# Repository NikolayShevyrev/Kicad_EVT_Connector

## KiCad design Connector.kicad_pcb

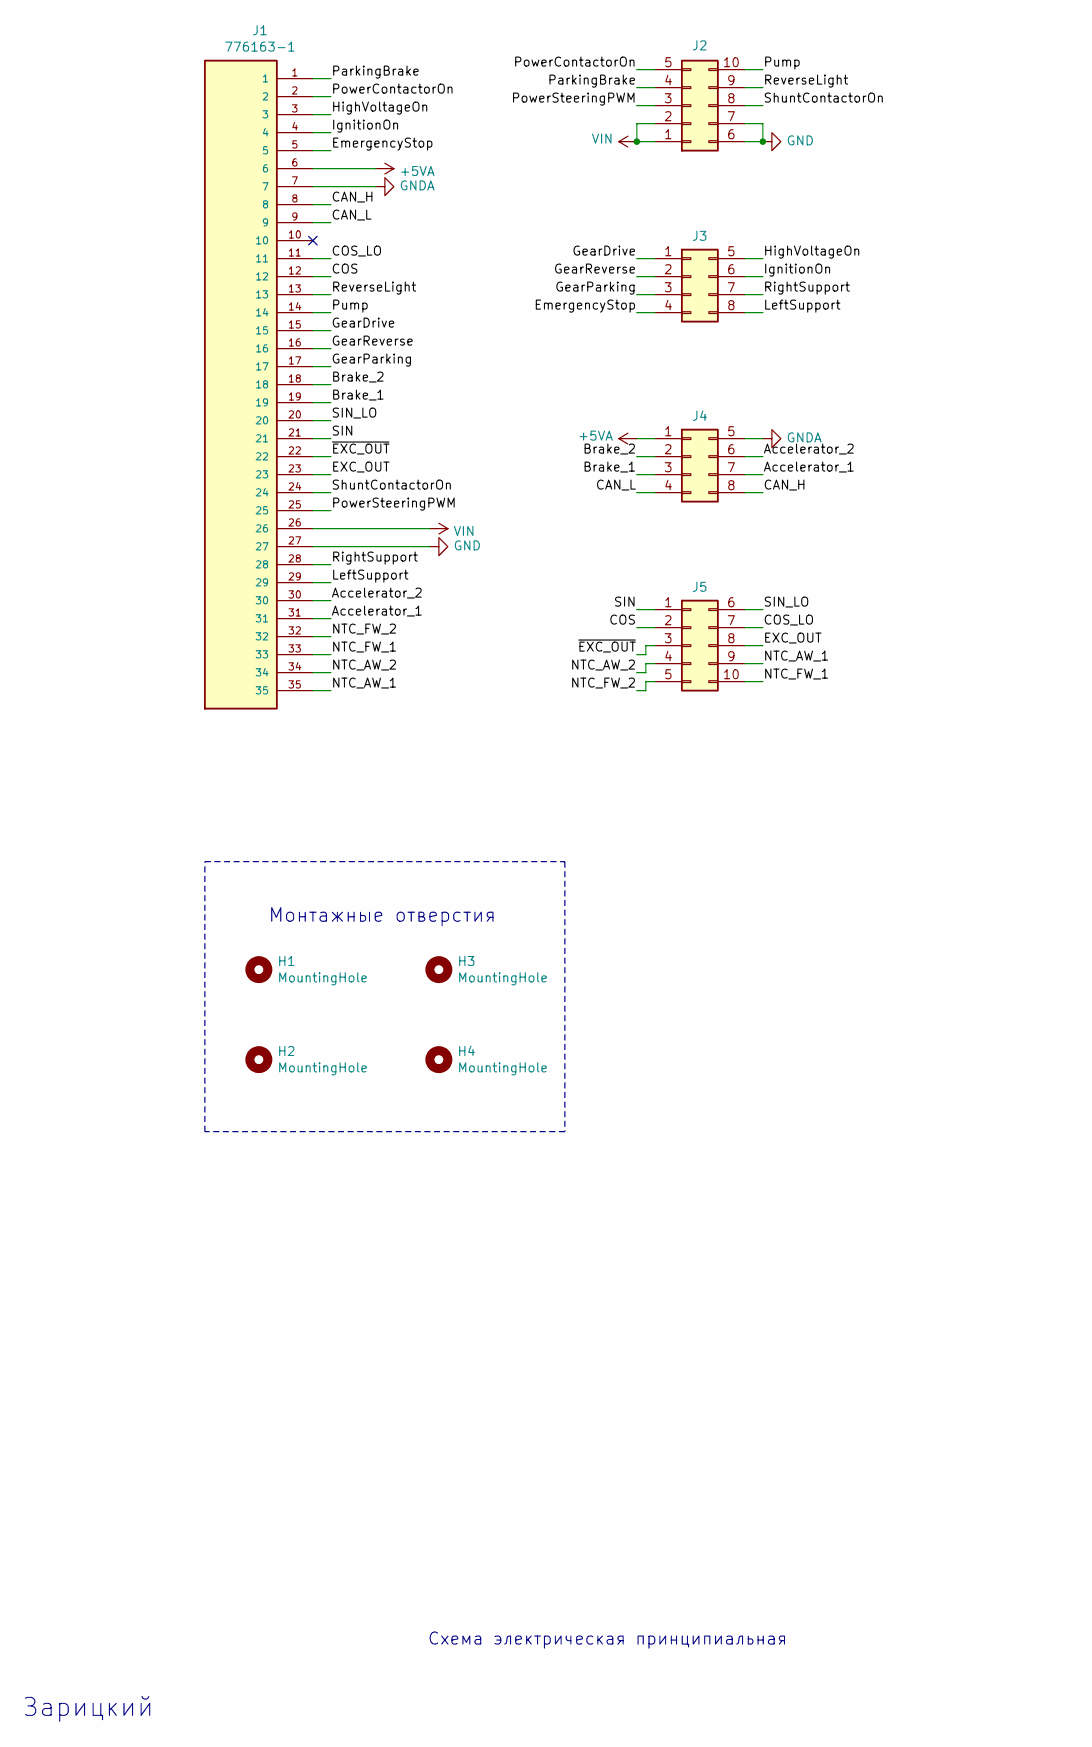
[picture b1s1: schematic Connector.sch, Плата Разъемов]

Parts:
H1, H2, H3, H4: MountingHole; MountingHole_4.5mm
J1: 776163-1; TE_776163-1
J2, J5: Conn_02x05_Top_Bottom; Molex_Micro-Fit_3.0_43045-1000_2x05_P3.00mm_Horizontal
J3, J4: Conn_02x04_Top_Bottom; Molex_Micro-Fit_3.0_43045-0800_2x04_P3.00mm_Horizontal

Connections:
+5VA: J1.6, J4.1
/Accelerator_1: J1.31, J4.7
/Accelerator_2: J1.30, J4.6
/Brake_1: J1.19, J4.3
/Brake_2: J1.18, J4.2
/CAN_H: J1.8, J4.8
/CAN_L: J1.9, J4.4
/COS: J1.12, J5.2
/COS_LO: J1.11, J5.7
/EXC_OUT: J1.23, J5.8
/EmergencyStop: J1.5, J3.4
/GearDrive: J1.15, J3.1
/GearParking: J1.17, J3.3
/GearReverse: J1.16, J3.2
/HighVoltageOn: J1.3, J3.5
/IgnitionOn: J1.4, J3.6
/LeftSupport: J1.29, J3.8
/NTC_AW_1: J1.35, J5.9
/NTC_AW_2: J1.34, J5.4
/NTC_FW_1: J1.33, J5.10
/NTC_FW_2: J1.32, J5.5
/ParkingBrake: J1.1, J2.4
/PowerContactorOn: J1.2, J2.5
/PowerSteeringPWM: J1.25, J2.3
/Pump: J1.14, J2.10
/ReverseLight: J1.13, J2.9
/RightSupport: J1.28, J3.7
/SIN: J1.21, J5.1
/SIN_LO: J1.20, J5.6
/ShuntContactorOn: J1.24, J2.8
/~EXC_OUT: J1.22, J5.3
GND: J1.27, J2.6, J2.7
GNDA: J1.7, J4.5
VDD: J1.26, J2.1, J2.2

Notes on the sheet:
Монтажные отверстия
Зарицкий
Схема электрическая принципиальная

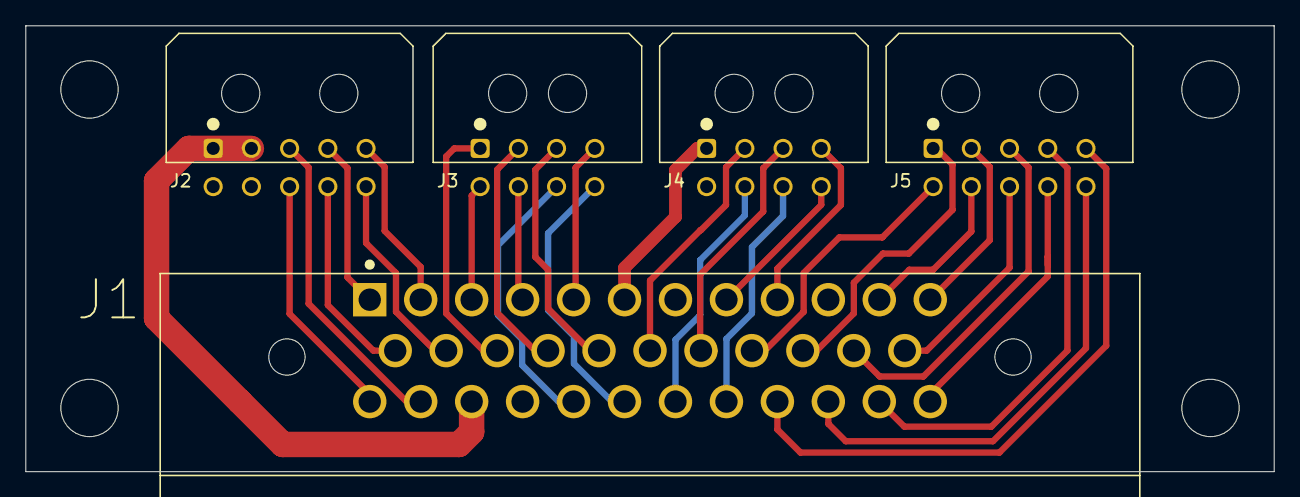
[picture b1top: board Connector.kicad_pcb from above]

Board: 2 copper layers, 98.0 x 35.0 mm, 9 parts (0 on the bottom side), 34 nets.

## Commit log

2021-07-21 Added pics
2021-08-03 Added IO Lables
2021-08-06 Lables revised
2021-08-16 Added PCB Outline
2021-08-19 Added Connector PinOut and PCB layout
2021-08-20 Added Gerbers
2021-08-23 Schematic: RevA, PCB: RevA, BOM: V1 RevA
2021-09-13 Added connector pinout
2021-10-06 Rev A, New logo
2021-10-12 RevA V2
2022-04-29 Added bom and schematic
2022-05-11 Added rd_converter inputs/outputs
2023-03-20 RevC
